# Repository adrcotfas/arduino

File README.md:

### Contents

####[groveColorSensor](https://github.com/adrcotfas/Arduino/tree/master/groveColorSensor)

Description:
- An Arduino library for the [Grove - I2C Color Sensor](http://www.seeedstudio.com/depot/grove-i2c-color-sensor-p-854.html?cPath=25_27)
- Supports the use of pre-measured or pre-calibrated colors for specific projects.
- Supports multiple color sensors used in parallel
- An example is provided for using two sensors with a 74HC4052 MUX

####[minimalDuino_107](https://github.com/adrcotfas/Arduino/tree/master/minimalDuino_107)

Description:
- PBC design for an Arduino Uno compatible board
- Single-sided, home-etchable with wide traces and 7 top jumper wires
- Compatible with shields designed to fit on top
- Different power connector options, 5V or 3.3V power regulation and options for crystal and caps or a resonator
- Power suply and debugging with FTDI breakout
- Better shield-friendliness by placing LEDs and the reset switch(side switch or top switch) at the edges of the board

Source: [Jeff's Arduino Blog](http://jmsarduino.blogspot.com)

####[minimalDuino_108](https://github.com/adrcotfas/Arduino/tree/master/minimalDuino_108)

Description:
- Simplified version tailored for my robotics projects
- Includes only 5V regulation
- Includes a power switch, usefull when you want your easily start/stop your robot

####[perceptrons3000](https://github.com/adrcotfas/Arduino/tree/master/perceptrons3000)

Description:
- Code excerpt and auxiliary PCB design from my project for the Continental Student Competition 2015 in Sibiu

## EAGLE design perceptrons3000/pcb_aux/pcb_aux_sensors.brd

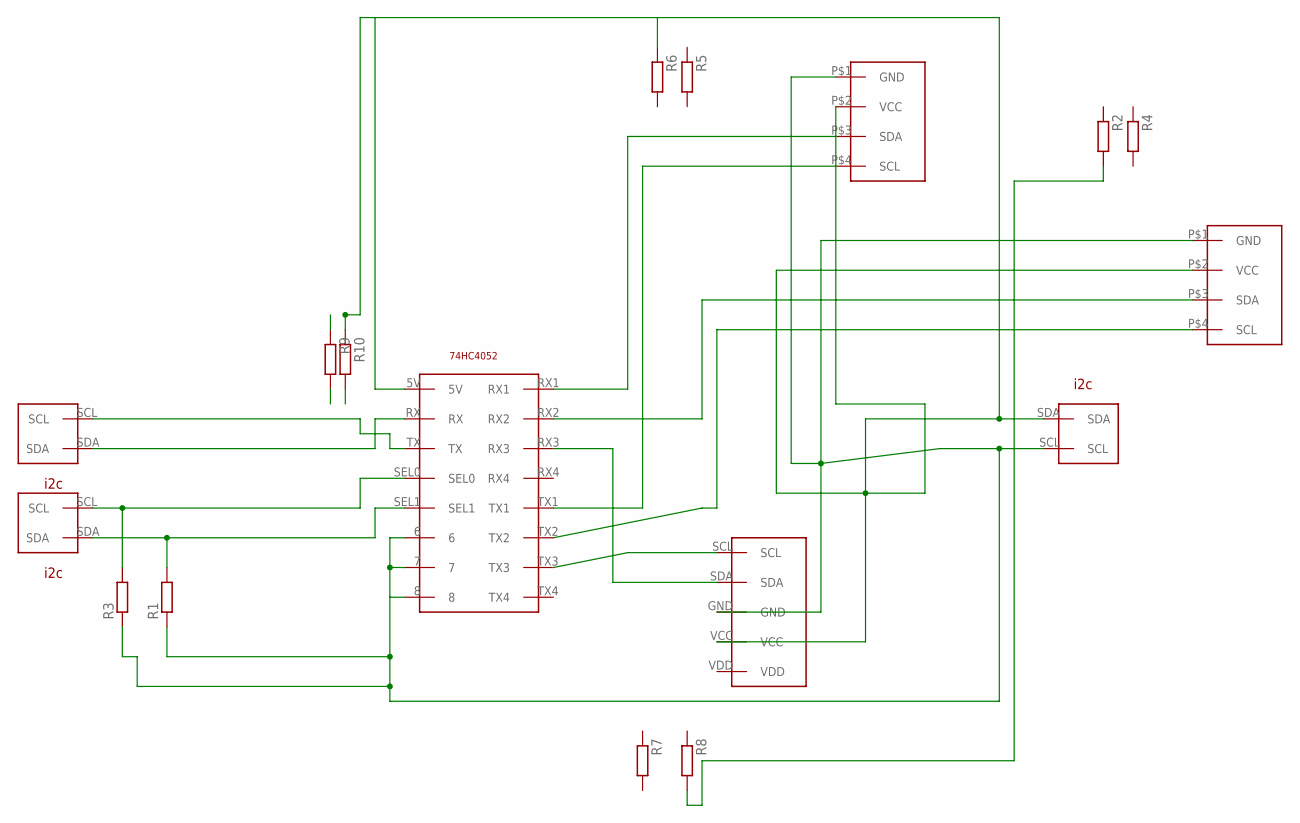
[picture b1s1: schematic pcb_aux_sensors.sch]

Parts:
I2C: I2C
MUXSELECT: I2C
PWR: I2C
R1, R2, R3, R4, R5, R6, R7, R8, R9, R10: R0204/7; 0204/7
U$2: 74HC4052
U$5, U$6: GROVECOLORSENSOR
U$7: MINIMU9_V4

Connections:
GND: PWR.SCL, R1.1, R3.1, U$2.6, U$2.7, U$2.8, U$5.P$1 (GND), U$6.P$1 (GND), U$7.GND
unnamed: I2C.SDA, U$2.RX
unnamed: I2C.SCL, U$2.TX
unnamed: U$2.RX1, U$5.P$3 (SDA)
unnamed: U$2.TX1, U$5.P$4 (SCL)
unnamed: U$2.RX2, U$6.P$3 (SDA)
unnamed: U$2.TX2, U$6.P$4 (SCL)
unnamed: U$2.RX3, U$7.SDA
unnamed: U$2.TX3, U$7.SCL
unnamed: MUXSELECT.SCL, R3.2, U$2.SEL0
unnamed: MUXSELECT.SDA, R1.2, U$2.SEL1
VCC: PWR.SDA, R2.2, R6.1, R8.2, R10.1, U$2.5V, U$5.P$2 (VCC), U$6.P$2 (VCC), U$7.VCC

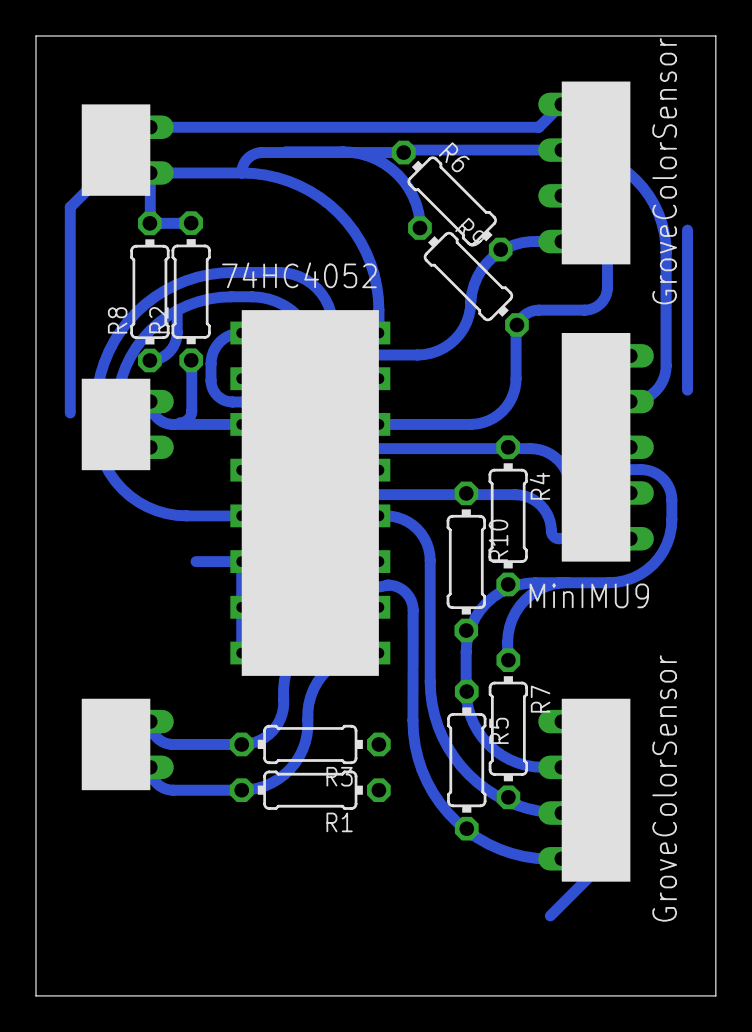
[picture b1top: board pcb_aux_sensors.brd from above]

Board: 2 copper layers, 37.8 x 53.3 mm, 17 parts (0 on the bottom side), 12 nets.

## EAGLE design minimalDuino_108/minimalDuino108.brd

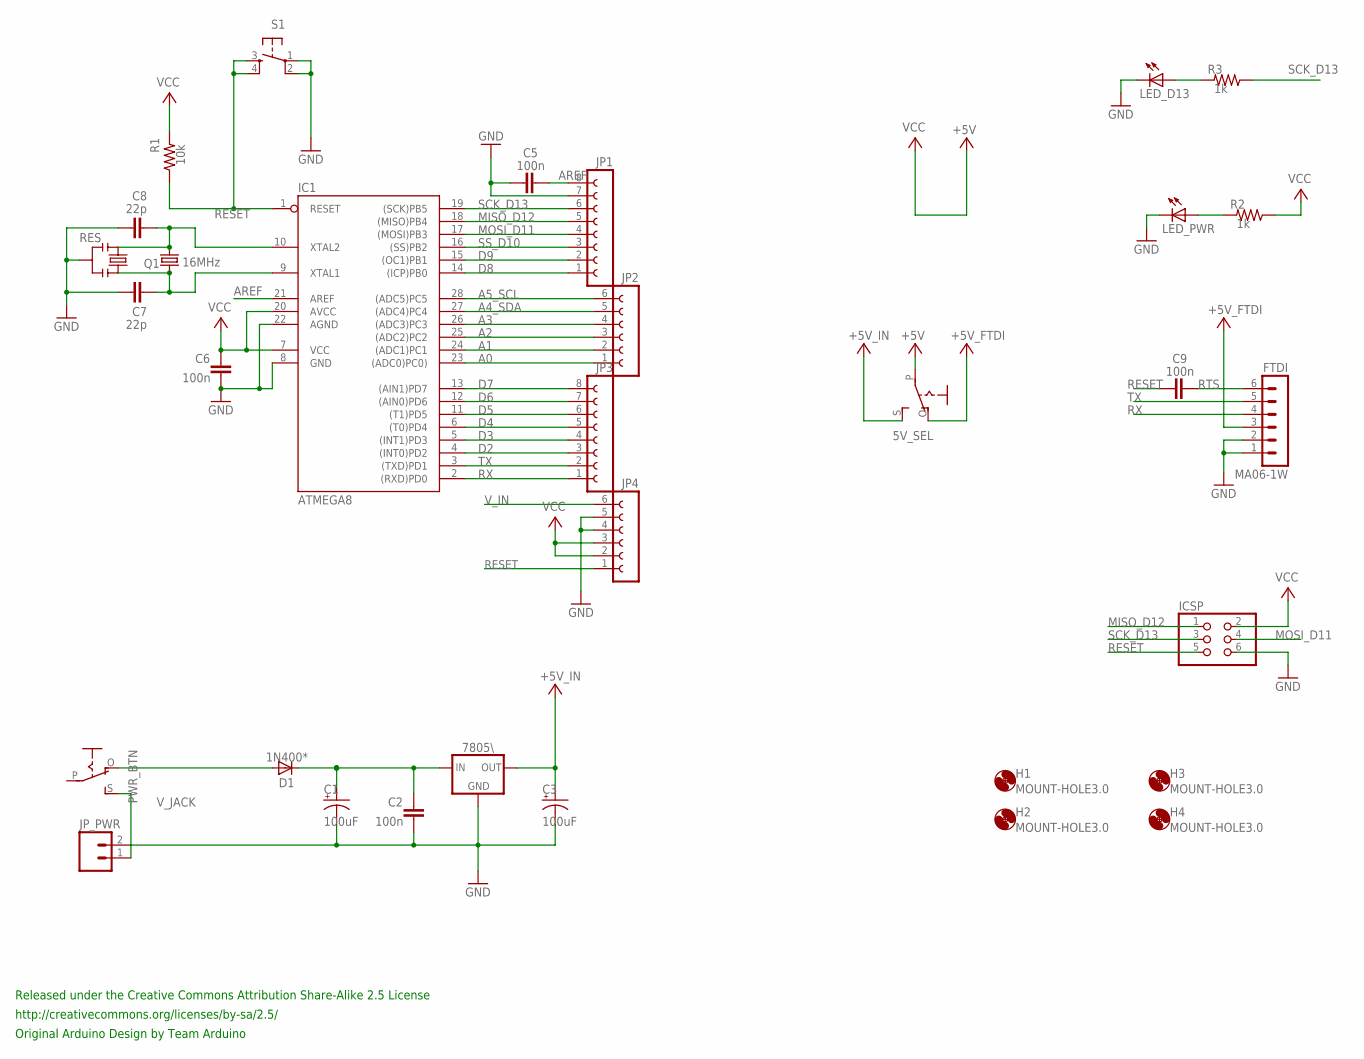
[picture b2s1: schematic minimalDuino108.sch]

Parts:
5V_SEL: EG1218S; EG1218
7805\: V_REG_78XXSIDE; 78XXL
C1: 100uF; E2,5-6E
C2, C5, C6, C9: 100n; C025-025X050
C3: 100uF; E2,5-6
C7, C8: 22p; C025-025X050
D1: 1N400*; DO35-10
FTDI: MA06-1W
H1, H2, H3, H4: MOUNT-HOLE3.0; 3,0
IC1: ATMEGA8; DIL28-3
ICSP: PINHD-2X3; 2X03
JP1, JP3: FE08-1; FE08
JP2, JP4: FE06-1; FE06
JP_PWR: M02PTH; 1X02
LED_D13: LED3MM
LED_PWR: LED3MM
PWR_BTN: EG1218S; EG1218
Q1: 16MHz; HC49/S
R1: 10k; 0204/7
R2, R3: 1k; 0204/7
RES: 16MHz; RESONATOR-PTH
S1: TAC_SWITCHPTH; TACTILE-PTH

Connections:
+5V: 5V_SEL.P
+5V_FTDI: 5V_SEL.O, FTDI.3
+5V_IN: 5V_SEL.S, 7805\.OUT, C3.+
A0: IC1.23 ((ADC0)PC0)), JP2.1
A1: IC1.24 ((ADC1)PC1), JP2.2
A2: IC1.25 ((ADC2)PC2), JP2.3
A3: IC1.26 ((ADC3)PC3), JP2.4
A4_SDA: IC1.27 ((ADC4)PC4), JP2.5
A5_SCL: IC1.28 ((ADC5)PC5), JP2.6
AREF: C5.2, IC1.21 (AREF), JP1.8
D2: IC1.4 ((INT0)PD2), JP3.3
D3: IC1.5 ((INT1)PD3), JP3.4
D4: IC1.6 ((T0)PD4), JP3.5
D5: IC1.11 ((T1)PD5), JP3.6
D6: IC1.12 ((AIN0)PD6), JP3.7
D7: IC1.13 ((AIN1)PD7), JP3.8
D8: IC1.14 ((ICP)PB0), JP1.1
D9: IC1.15 ((OC1)PB1), JP1.2
GND: 7805\.GND, C1.-, C2.2, C3.-, C5.1, C6.2, C7.1, C8.1, FTDI.1, FTDI.2, IC1.8 (GND), IC1.22 (AGND), ICSP.6, JP1.7, JP4.4, JP4.5, JP_PWR.2, LED_D13.K (C), LED_PWR.K (C), RES.2, S1.1, S1.2
MISO_D12: IC1.18 ((MISO)PB4), ICSP.1, JP1.5
MOSI_D11: IC1.17 ((MOSI)PB3), ICSP.4, JP1.4
unnamed: LED_PWR.A, R2.2
unnamed: JP_PWR.1, PWR_BTN.S
unnamed: LED_D13.A, R3.2
unnamed: C7.2, IC1.9 (XTAL1), Q1.1, RES.3
unnamed: C8.2, IC1.10 (XTAL2), Q1.2, RES.1
RESET: C9.2, IC1.1 (RESET), ICSP.5, JP4.1, R1.1, S1.3, S1.4
RTS: C9.1, FTDI.6
RX: FTDI.4, IC1.2 ((RXD)PD0), JP3.1
SCK_D13: IC1.19 ((SCK)PB5), ICSP.3, JP1.6, R3.1
SS_D10: IC1.16 ((SS)PB2), JP1.3
TX: FTDI.5, IC1.3 ((TXD)PD1), JP3.2
VCC: C6.1, IC1.7 (VCC), IC1.20 (AVCC), ICSP.2, JP4.2, JP4.3, R1.2, R2.1
V_IN: 7805\.IN, C1.+, C2.1, D1.C, JP4.6
V_JACK: D1.A, PWR_BTN.O

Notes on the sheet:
Released under the Creative Commons Attribution Share-Alike 2.5 License
http://creativecommons.org/licenses/by-sa/2.5/
Original Arduino Design by Team Arduino

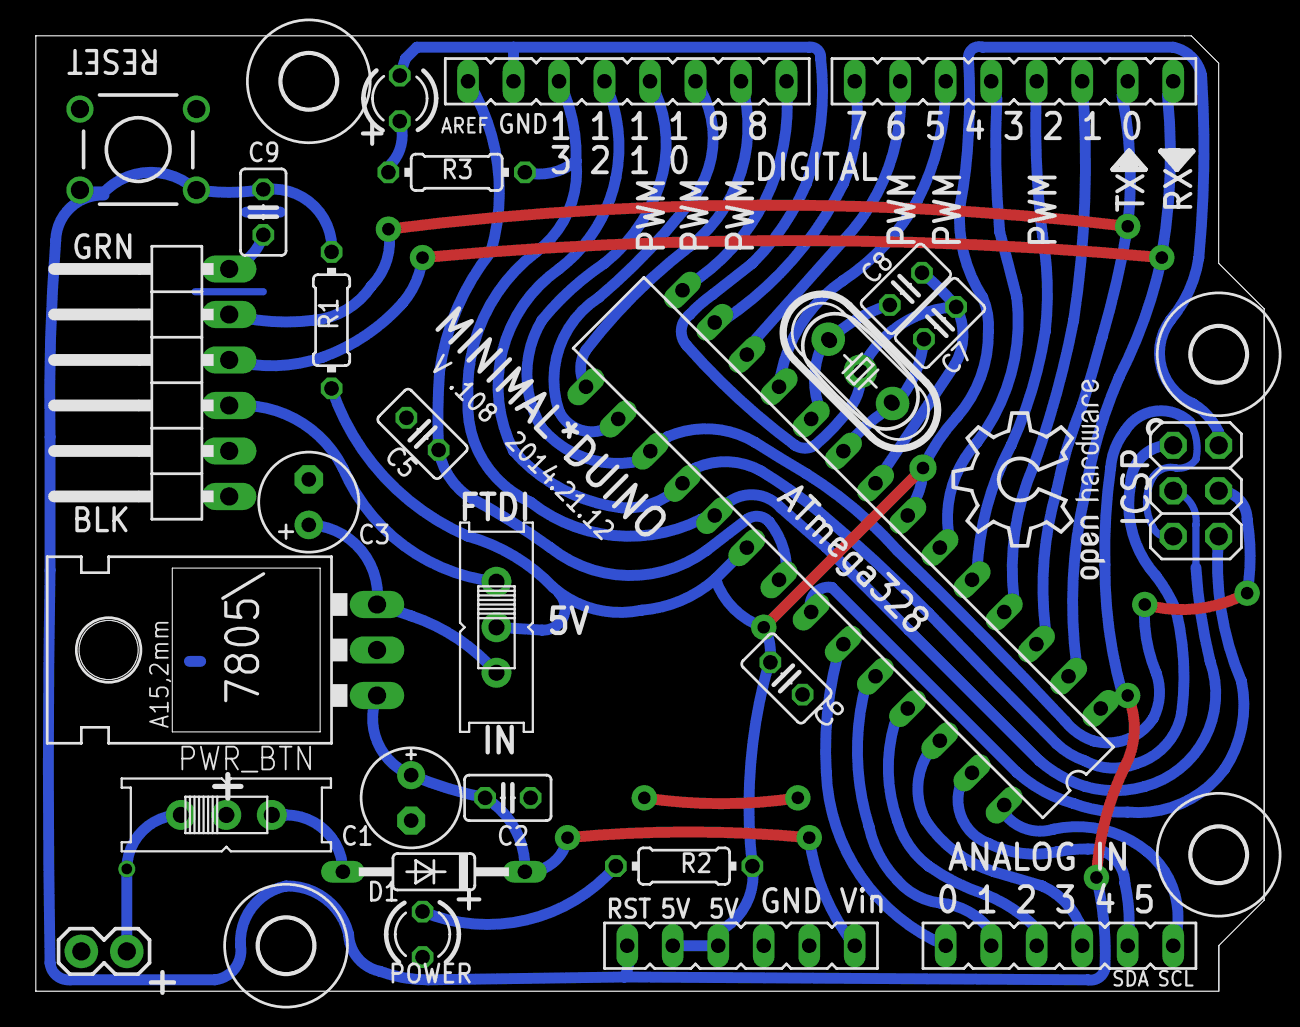
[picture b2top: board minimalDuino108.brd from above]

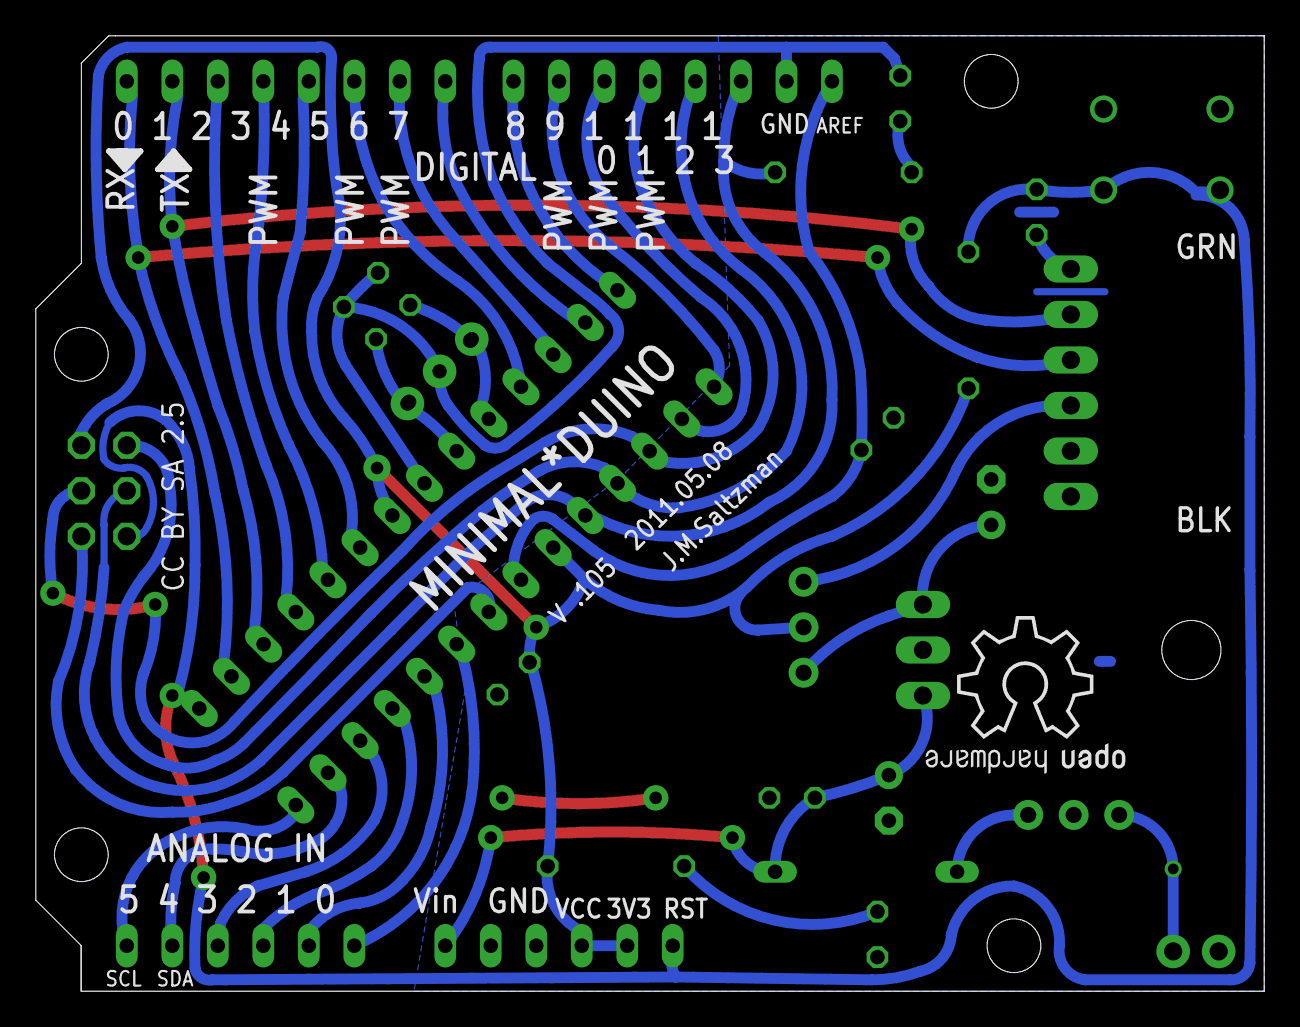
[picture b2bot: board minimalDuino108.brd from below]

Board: 2 copper layers, 68.6 x 53.3 mm, 36 parts (2 on the bottom side), 34 nets.

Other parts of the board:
U$1, U$4: OSHW_TEXT_.3
U$2, U$3: OSHW_GEAR_HOLLOW_.3

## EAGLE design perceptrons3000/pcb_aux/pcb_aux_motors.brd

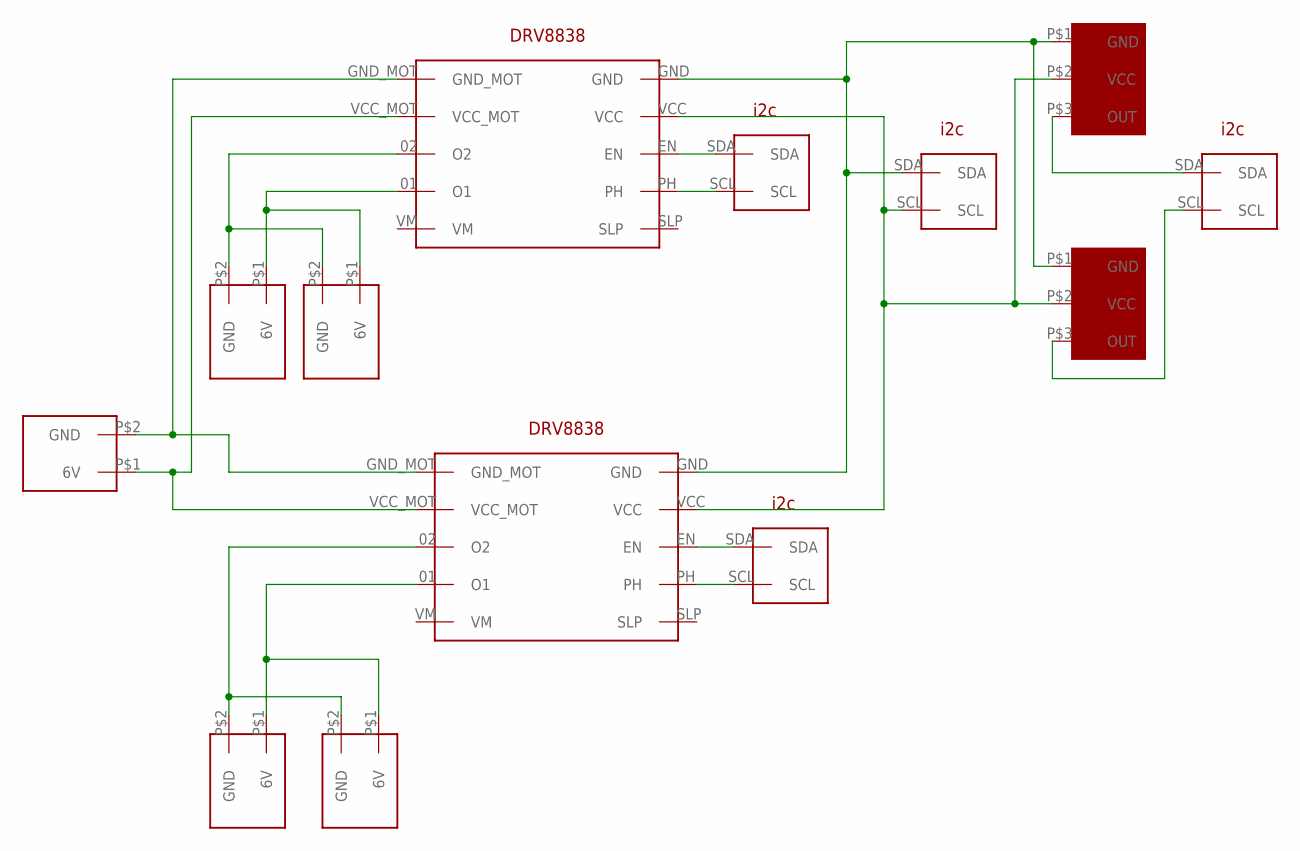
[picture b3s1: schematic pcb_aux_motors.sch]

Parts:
EN/PH1, EN/PH2: I2C
ENCODERS: I2C
U$1, U$8, U$9, U$10, U$11: MOTOR
U$2, U$3: ENCODER
U$4, U$12: DRV8838
VCC/GND: I2C

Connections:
GND: U$2.P$1 (GND), U$3.P$1 (GND), U$4.GND, U$12.GND, VCC/GND.SDA
unnamed: ENCODERS.SDA, U$2.P$3 (OUT)
unnamed: ENCODERS.SCL, U$3.P$3 (OUT)
unnamed: U$1.P$2 (GND), U$4.02 (O2), U$8.P$2 (GND)
unnamed: U$1.P$1 (6V), U$4.01 (O1), U$8.P$1 (6V)
unnamed: U$9.P$2 (GND), U$10.P$2 (GND), U$12.02 (O2)
unnamed: U$9.P$1 (6V), U$10.P$1 (6V), U$12.01 (O1)
unnamed: U$4.GND_MOT, U$11.P$2 (GND), U$12.GND_MOT
unnamed: U$4.VCC_MOT, U$11.P$1 (6V), U$12.VCC_MOT
unnamed: EN/PH1.SDA, U$4.EN
unnamed: EN/PH1.SCL, U$4.PH
unnamed: EN/PH2.SDA, U$12.EN
unnamed: EN/PH2.SCL, U$12.PH
VCC: U$2.P$2 (VCC), U$3.P$2 (VCC), U$4.VCC, U$12.VCC, VCC/GND.SCL

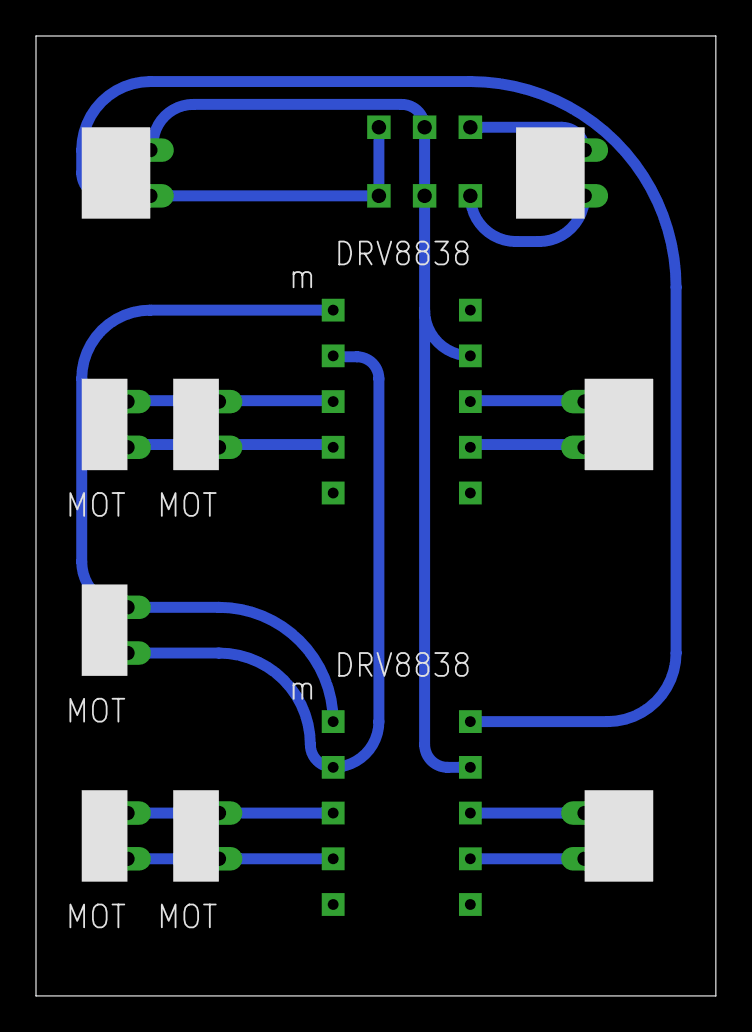
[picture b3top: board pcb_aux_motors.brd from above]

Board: 2 copper layers, 37.8 x 53.3 mm, 13 parts (0 on the bottom side), 14 nets.

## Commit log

2016-06-08 :lollipop: Added .gitattributes & .gitignore files
2016-06-08 initial commit after clean-up

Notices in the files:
minimalDuino_108/minimalDuino108.brd:
CC BY SA 2.5
